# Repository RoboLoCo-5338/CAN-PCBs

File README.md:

# Quick Overview
The goal of this project was to create a Printed Circuit Board (PCB) for our Controller Area Network (CAN) Bus using a star topology for our robot.
You can learn more CAN and various topologies [here](http://www.mindsensors.com/content/86-can-and-its-topology).
Each v7 and v8 board was designed to accommodate up to **10** CAN devices, i.e., 8 Victor SPXs or Talon SRXs along with a Power Distribution Panel and RoboRIO.
The v9 board allows for up to **24** connections per board including a "ground" connection for each. 

Easy expansion is possible by linking multiple boards to each other directly to increase the total number of connections, i.e., 2 boards allows for 18 total connections.
When combined with code that is fault-tolerant, it can be possible to recover from the loss or disconnection of a device on the bus, which would be catastrophic on a daisy-chained network.

This project contains two folders, one for the PCB that our team currently uses on our competition robot, as well as one for the PCB that we plan to handout at the Chesapeake District Championships.

We have used these boards since the 2017/2018 season and are satisfied with their excellent performance and ease of wiring.

# RoboLoCo
* [RoboLoCo's Website](https://www.roboloco.org)
* [CAN PCB Website](https://www.roboloco.org/canpcb)

# PCB Specifics
The PCB uses screw terminals to connect devices to the bus.
They, such as the ones we use from [Amazon](https://www.amazon.com/gp/product/B00EZ3QPCU/), are standard Wago 237-132 screw terminals.
We have found it ideal when the CAN wires are placed in ferrules, such as the ones we use from [Automation Direct](https://www.automationdirect.com/adc/Shopping/Catalog/Wiring_Solutions/BM_Group_-_Wire_End_Connectors/Insulated_Ferrules/DIN_Color_Single_Wire/BM-00601), but that is not required.
The terminating 120Ω resistors are optional in almost every use case and are for extra future functionality to not require the use of two devices with built in termination.
However, should a 120Ω resistors be added, its corresponding optional male headers **must** be added to enable or disable the resistors.

# Holder and Mounting Info
The PCBs' holders were also designed to fit on standard 1" pegboard via zip ties or bolts.
The holes on each holder was designed to accommodate heat-set inserts, such as the ones we use from [McMaster-Carr](https://www.mcmaster.com/#93365a132/=1b46wa6), to provide threaded holes.
The board then uses at up to 6 0.1875" #6-32 bolts depending on the PCB, such as the ones we use from [McMaster-Carr](https://www.mcmaster.com/#91864a085/), to be anchored down.
Particularly, the spacing around the center holes allows for the use of thumb screws, such as the ones we use from [Amazon](https://www.amazon.com/Anodized-Aluminum-Computer-Thumbscrews-Thread/dp/B00BGZ1OFI/), to allow for easier insertion and removal before final mounting.

# Files
For each board, the files provided include the Eagle BRD, SCH, and EPF files, as well as STL files for the 3D printed holder.
The files are compatible with [Eagle](https://www.autodesk.com/products/eagle/free-download) 8.0 and up.
The DRU file used by our PCB fab, [Silver Circuits](http://www.custompcb.com), is also provided. However, the Eagles files can be used to manufacture the board with the PCB fab of your choice
For each board, there are also images of the board layout and schematic in Eagle, a render of the holder, and images of the actual PCB in the 3D-printed holder.

# Versions

## Star Board v7 (aka Competition PCB)
This is a current production board that is tested and in use on RoboLoCo's 2019 robot. 

## Star Board v8
This is incomplete and under active development. 

## Star Board Wide v9
### Overview
This is a current production board that is tested and in use on RoboLoCo's 2020 robot. 

### "Ground" Connection
For FRC the "ground" on the board should be used with the sheild on sheilded twisted pair cable. RoboLoCo is leaving it to float. 
It's possible to attach to either the neg power or chassis. However both options carry slight risks during inspection. If attached to the 
chassis any instance of the shield touching **any** electrical connections even slightly will cause the chassis to be electrically connected 
to the electrical system. A related issue happens if using the chassis for the sheild. 

# Final Notes
If you have any questions, feel reach out and contact us at contact@roboloco.org.
Please share with us your experiences if you use them and any feedback you have!

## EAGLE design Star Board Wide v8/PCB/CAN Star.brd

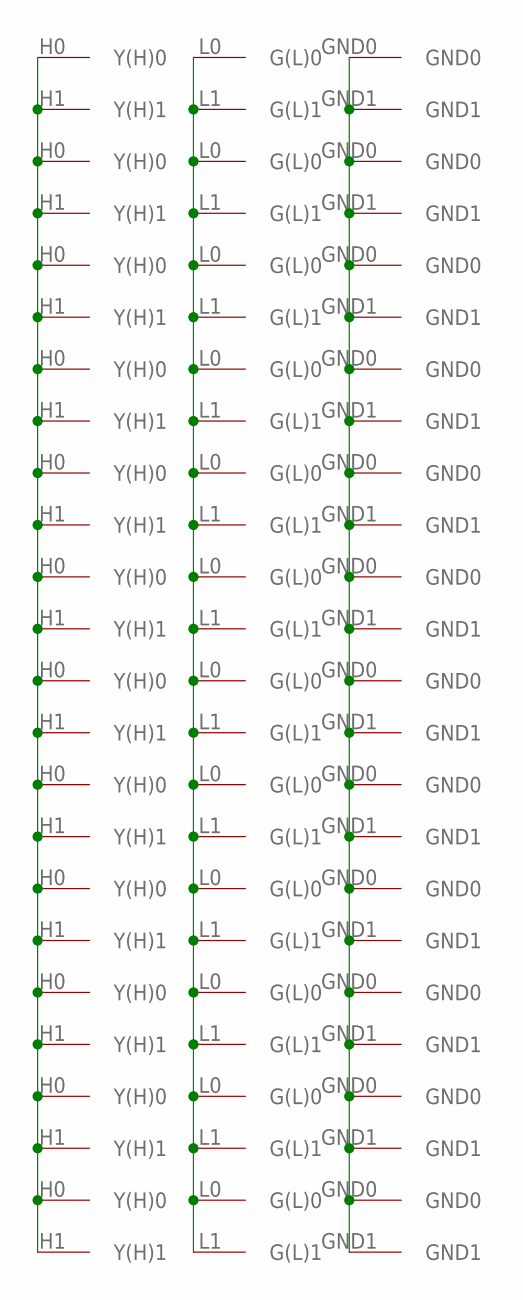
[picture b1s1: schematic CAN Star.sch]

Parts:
U$1, U$2, U$3, U$4, U$5, U$6, U$7, U$8, U$9, U$10, U$11, U$12: 2-3-TERMS; GREEN-2-TERMS

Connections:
G(L): U$1.L0 (G(L)0), U$1.L1 (G(L)1), U$2.L0 (G(L)0), U$2.L1 (G(L)1), U$3.L0 (G(L)0), U$3.L1 (G(L)1), U$4.L0 (G(L)0), U$4.L1 (G(L)1), U$5.L0 (G(L)0), U$5.L1 (G(L)1), U$6.L0 (G(L)0), U$6.L1 (G(L)1), U$7.L0 (G(L)0), U$7.L1 (G(L)1), U$8.L0 (G(L)0), U$8.L1 (G(L)1), U$9.L0 (G(L)0), U$9.L1 (G(L)1), U$10.L0 (G(L)0), U$10.L1 (G(L)1), U$11.L0 (G(L)0), U$11.L1 (G(L)1), U$12.L0 (G(L)0), U$12.L1 (G(L)1)
GND: U$1.GND0, U$1.GND1, U$2.GND0, U$2.GND1, U$3.GND0, U$3.GND1, U$4.GND0, U$4.GND1, U$5.GND0, U$5.GND1, U$6.GND0, U$6.GND1, U$7.GND0, U$7.GND1, U$8.GND0, U$8.GND1, U$9.GND0, U$9.GND1, U$10.GND0, U$10.GND1, U$11.GND0, U$11.GND1, U$12.GND0, U$12.GND1
Y(H): U$1.H0 (Y(H)0), U$1.H1 (Y(H)1), U$2.H0 (Y(H)0), U$2.H1 (Y(H)1), U$3.H0 (Y(H)0), U$3.H1 (Y(H)1), U$4.H0 (Y(H)0), U$4.H1 (Y(H)1), U$5.H0 (Y(H)0), U$5.H1 (Y(H)1), U$6.H0 (Y(H)0), U$6.H1 (Y(H)1), U$7.H0 (Y(H)0), U$7.H1 (Y(H)1), U$8.H0 (Y(H)0), U$8.H1 (Y(H)1), U$9.H0 (Y(H)0), U$9.H1 (Y(H)1), U$10.H0 (Y(H)0), U$10.H1 (Y(H)1), U$11.H0 (Y(H)0), U$11.H1 (Y(H)1), U$12.H0 (Y(H)0), U$12.H1 (Y(H)1)

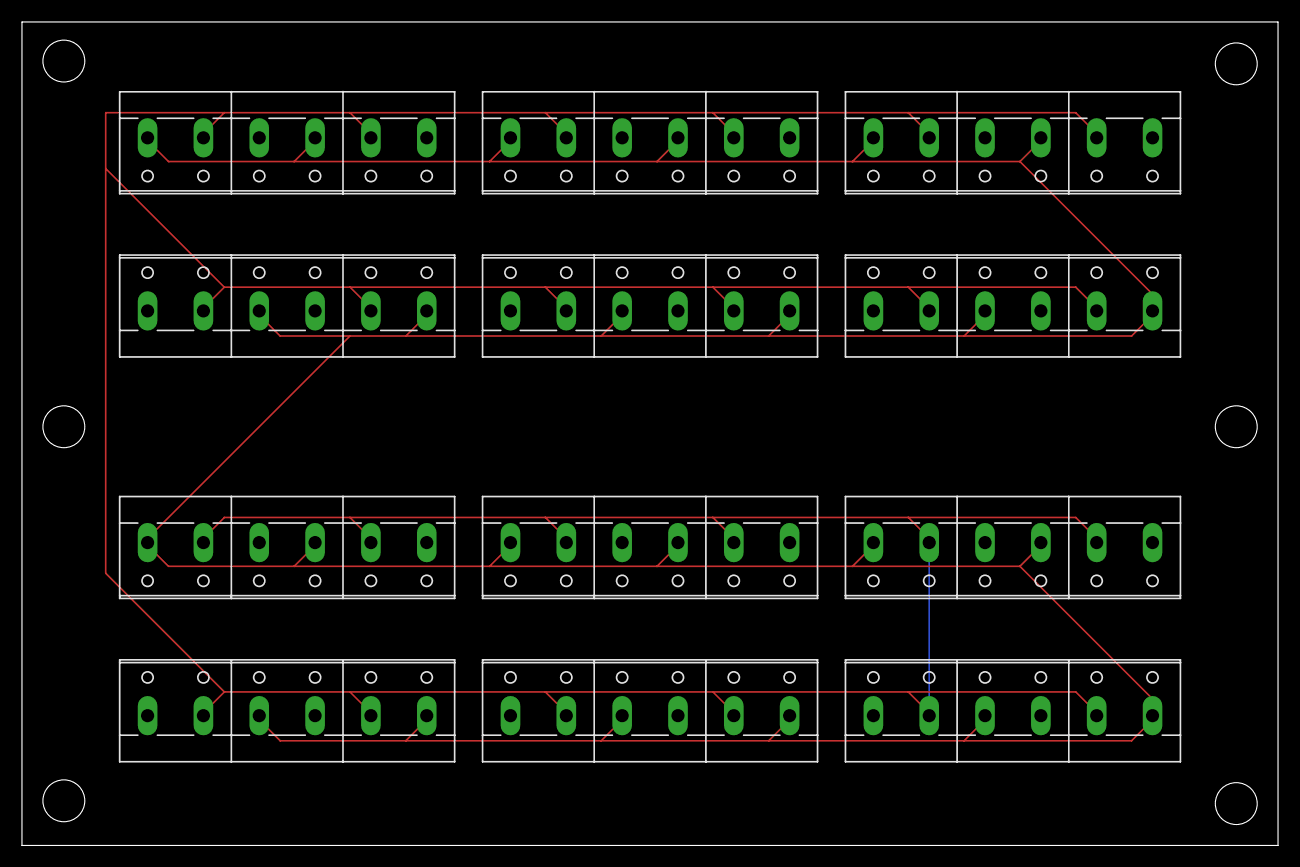
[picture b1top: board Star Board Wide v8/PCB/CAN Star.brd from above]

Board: 2 copper layers, 114.3 x 74.9 mm, 12 parts (0 on the bottom side), 3 nets.

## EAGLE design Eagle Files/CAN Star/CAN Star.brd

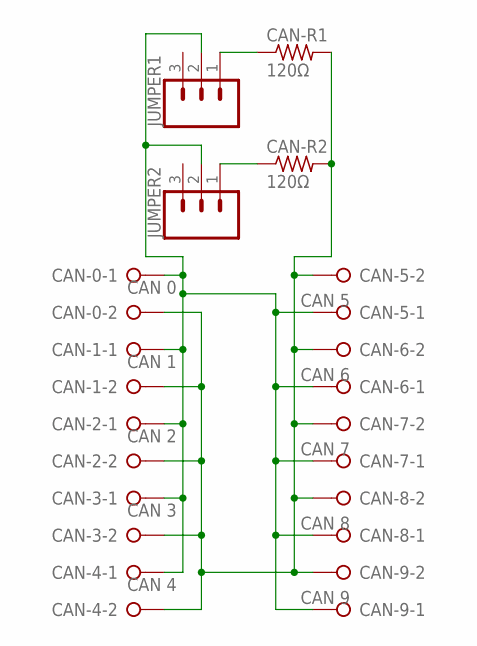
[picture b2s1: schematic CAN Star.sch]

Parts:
CAN-0: CAN 0; W237-132
CAN-1: CAN 1; W237-132
CAN-2: CAN 2; W237-132
CAN-3: CAN 3; W237-132
CAN-4: CAN 4; W237-132
CAN-5: CAN 5; W237-132
CAN-6: CAN 6; W237-132
CAN-7: CAN 7; W237-132
CAN-8: CAN 8; W237-132
CAN-9: CAN 9; W237-132
CAN-R1, CAN-R2: 120Ω; 0207/10
JUMPER1, JUMPER2: CONN_03; 1X03

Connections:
CAN-A: CAN-0.1, CAN-1.1, CAN-2.1, CAN-3.1, CAN-4.1, CAN-5.1, CAN-6.1, CAN-7.1, CAN-8.1, CAN-9.1, JUMPER1.2, JUMPER2.2
CAN-B: CAN-0.2, CAN-1.2, CAN-2.2, CAN-3.2, CAN-4.2, CAN-5.2, CAN-6.2, CAN-7.2, CAN-8.2, CAN-9.2, CAN-R1.2, CAN-R2.2
unnamed: CAN-R1.1, JUMPER1.1
unnamed: CAN-R2.1, JUMPER2.1

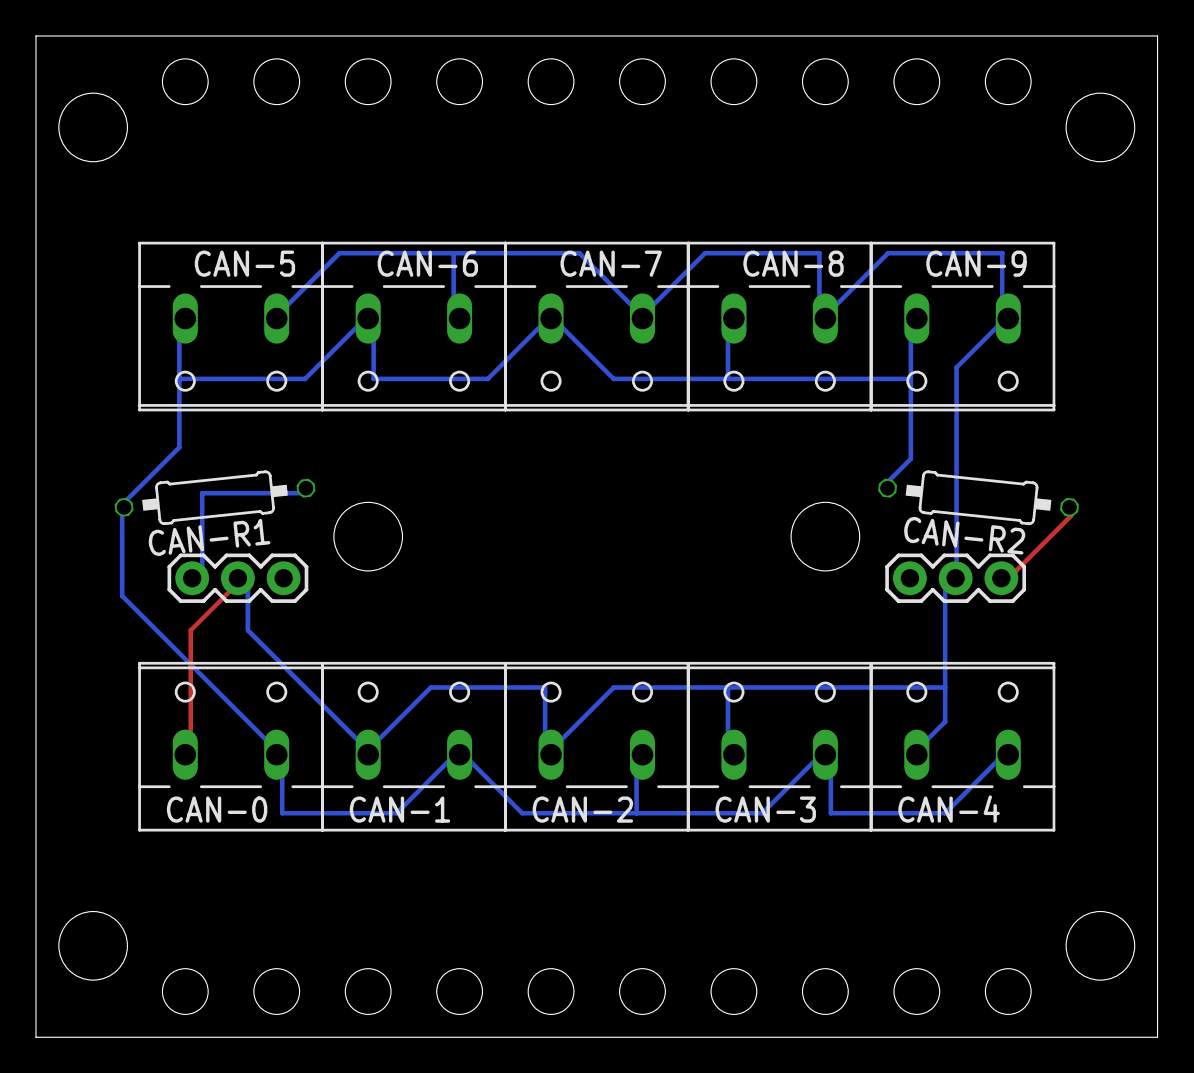
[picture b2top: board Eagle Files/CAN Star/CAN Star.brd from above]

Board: 2 copper layers, 62.3 x 55.6 mm, 14 parts (0 on the bottom side), 4 nets.

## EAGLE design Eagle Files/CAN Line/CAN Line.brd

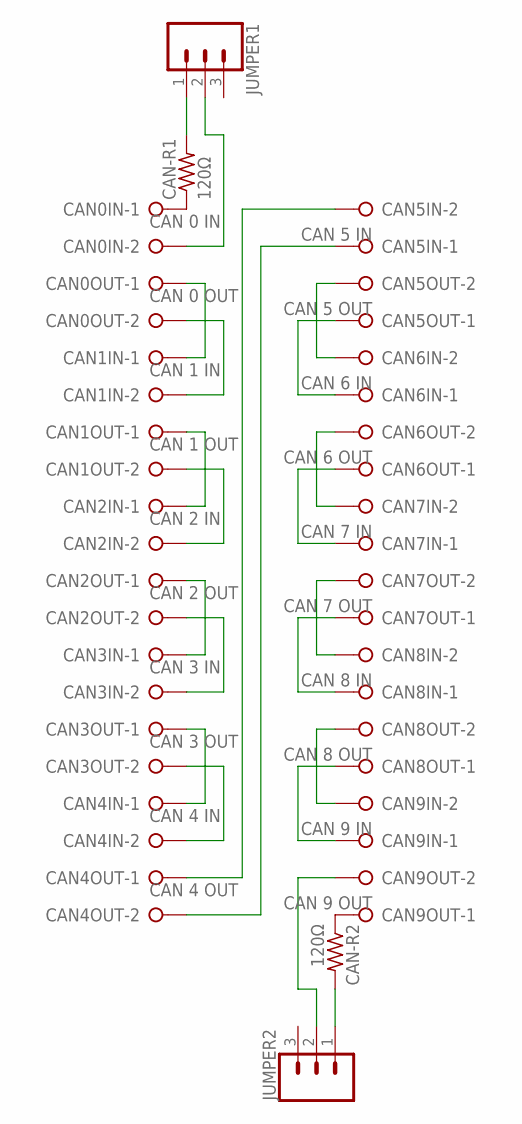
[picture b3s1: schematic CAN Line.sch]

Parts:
CAN0IN: CAN 0 IN; W237-132
CAN0OUT: CAN 0 OUT; W237-132
CAN1IN: CAN 1 IN; W237-132
CAN1OUT: CAN 1 OUT; W237-132
CAN2IN: CAN 2 IN; W237-132
CAN2OUT: CAN 2 OUT; W237-132
CAN3IN: CAN 3 IN; W237-132
CAN3OUT: CAN 3 OUT; W237-132
CAN4IN: CAN 4 IN; W237-132
CAN4OUT: CAN 4 OUT; W237-132
CAN5IN: CAN 5 IN; W237-132
CAN5OUT: CAN 5 OUT; W237-132
CAN6IN: CAN 6 IN; W237-132
CAN6OUT: CAN 6 OUT; W237-132
CAN7IN: CAN 7 IN; W237-132
CAN7OUT: CAN 7 OUT; W237-132
CAN8IN: CAN 8 IN; W237-132
CAN8OUT: CAN 8 OUT; W237-132
CAN9IN: CAN 9 IN; W237-132
CAN9OUT: CAN 9 OUT; W237-132
CAN-R1, CAN-R2: 120Ω; 0207/10
JUMPER1, JUMPER2: CONN_03; 1X03

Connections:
unnamed: CAN0IN.1, CAN-R1.1
unnamed: CAN0IN.2, JUMPER1.2
unnamed: CAN0OUT.1, CAN1IN.1
unnamed: CAN0OUT.2, CAN1IN.2
unnamed: CAN1OUT.1, CAN2IN.1
unnamed: CAN1OUT.2, CAN2IN.2
unnamed: CAN2OUT.1, CAN3IN.1
unnamed: CAN2OUT.2, CAN3IN.2
unnamed: CAN3OUT.1, CAN4IN.1
unnamed: CAN3OUT.2, CAN4IN.2
unnamed: CAN4OUT.1, CAN5IN.2
unnamed: CAN4OUT.2, CAN5IN.1
unnamed: CAN5OUT.2, CAN6IN.2
unnamed: CAN5OUT.1, CAN6IN.1
unnamed: CAN6OUT.2, CAN7IN.2
unnamed: CAN6OUT.1, CAN7IN.1
unnamed: CAN7OUT.2, CAN8IN.2
unnamed: CAN7OUT.1, CAN8IN.1
unnamed: CAN8OUT.2, CAN9IN.2
unnamed: CAN8OUT.1, CAN9IN.1
unnamed: CAN9OUT.2, JUMPER2.2
unnamed: CAN9OUT.1, CAN-R2.1
unnamed: CAN-R2.2, JUMPER2.1
unnamed: CAN-R1.2, JUMPER1.1

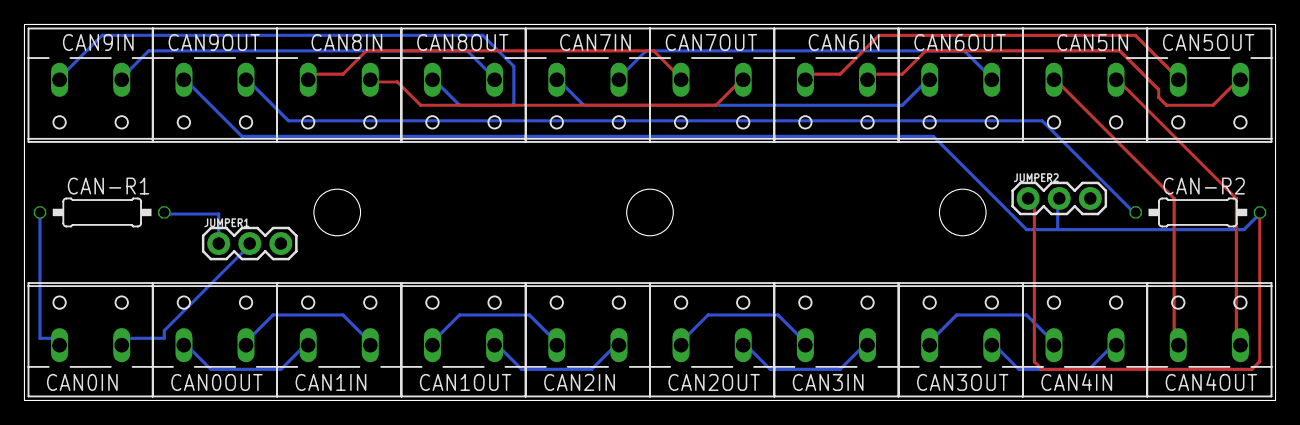
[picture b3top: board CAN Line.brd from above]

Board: 2 copper layers, 102.3 x 30.7 mm, 24 parts (0 on the bottom side), 24 nets.

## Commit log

2017-12-09 Initial File Uploads
2017-12-15 Updated Eagle Files
2017-12-18 Updated with strain relief holes, but not finalized yet.
2017-12-23 Finalized Star PCB
2017-12-23 Added additional mounting holes
2017-12-24 Removed old files
2017-12-25 Finalized Star PCB Design
2017-12-25 Actually uploaded the right version ;)
2017-12-25 Beginning update of Line PCB and Holder
2017-12-26 Added SilverCircuits DRU file
2018-01-11 Updated Star PCB design and added finalized holder
2018-01-13 Updated dimensions of holder slightly to improve fit and support
2018-01-14 Updated STL, Images, Eagle Files, and the README to make it more descriptive and informative
2018-01-15 Updated README, adjusted holder, and cleaned up github repo
2018-01-16 Added photos of final product
2018-02-04 Updated README, renamed files, improved holder STL export, added additional images
2018-02-04 Cleaning up README
2018-02-04 Finalized README
2018-02-04 Finished README
2018-02-04 Fixed link.
2018-03-15 Updated to the version that we are planning on handing out at District Champs
2018-03-19 Prepared folders and layout to contain two PCB versions, the one we hand out and one we personally use.
2018-03-20 Updated with finalized files for District Champs PCB Gift, including a new holder stl and image, along with a smaller board with the url on it eagle files and image.
2018-03-20 Test
2018-03-21 Adjusted folder names and holders
2018-03-21 Updated README and renders
2018-05-06 Updated folder structure and made sure the correct .brd/.sch files were in the system so that future reorders by the team will be correct
2019-02-18 Fixed contact email
2019-02-27 Added links to roboloco's website
2019-02-27 Added license
    OK'ed by Arvind via discord
2019-02-27 Ignoring some unwanted files
2019-02-27 Don't want this
2019-02-27 Updated photos
2019-02-27 Adding skel for Star Board v8
2019-02-27 Cleanup
2019-02-27 Don't want backup boards
2019-02-27 Created StarBoard v8
2019-02-27 Created v8 wide board
2019-02-27 Unlocked and fixed view
2019-02-27 doc clarification
2019-08-10 switch to wide-v9, add in grounds, removed odd connections, needs layout work
2019-08-10 change layout to 3 by 4
2019-11-24 Remade board wide v9
2019-11-24 Auto routed
2019-11-24 Rerouted with better nets for gnd
2020-01-12 Reduced lengh so that it'll be producible by custompbc.com
2020-01-12 Updated some info
2020-01-12 Updated with ground pour
2020-01-12 Updated image
2020-01-12 Added copper pour to top layer too
2020-01-12 Updated misc files
2020-01-27 Cleanup and wide v8 rename to v9
2020-01-27 Rename of comp pcb -> v7 & doc update for wide v9
2020-01-27 doc++
2020-01-27 Fixed doc versions
2020-01-27 Corrected doc for used-since date
2022-03-13 Added Fab Files
2022-03-13 updated Readme.txt with additional detail
2023-01-19 Updated web address on silkscreen
2024-01-27 upload
2024-01-28 upload datasheet
2024-01-28 update design file
2024-02-25 add PDFs

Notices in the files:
parts and their libraries:
SparkFun-Connectors: Licensing: Creative Commons ShareAlike 4.0 International - https://creativecommons.org/licenses/by-sa/4.0
